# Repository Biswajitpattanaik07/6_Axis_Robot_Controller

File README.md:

# Axion: 6-Axis Robot Arm Controller

Axion is an open-source controller board for a 6-axis articulated robot arm. It is built around an **STM32F103C8T6** and combines six servo outputs, six per-joint IMU inputs, and three ways to talk to the outside world: USB, CAN bus, and an NRF24L01 wireless link.

The whole board runs from a single **12 V** input. Everything else (5 V for servos and logic, 3.3 V for the MCU and radio) is generated on board.

---

## Table of contents

1. [Features](#features)
2. [System overview](#system-overview)
3. [Hardware details](#hardware-details)
4. [Pin mapping](#pin-mapping)
5. [Power design notes](#power-design-notes)
6. [PCB gallery](#pcb-gallery)
7. [Repository structure](#repository-structure)
8. [Bill of materials](#bill-of-materials)
9. [Getting started](#getting-started)
10. [Firmware](#firmware)
11. [Known limitations and design notes](#known-limitations-and-design-notes)
12. [Roadmap](#roadmap)
13. [Contributing](#contributing)
14. [License](#license)

---

## Features

| Area | What the board provides |
|---|---|
| Controller | STM32F103C8T6 (ARM Cortex-M3) |
| Servo outputs | 6 channels, each with its own MOSFET driver stage |
| Orientation feedback | 6 I2C headers, one per joint, for IMUs |
| USB | CP2102N USB-to-UART bridge |
| CAN | TCAN330 CAN transceiver |
| Wireless | NRF24L01 socket |
| Power input | 12 V |
| 5 V rail | TPS5331x buck converter |
| 3.3 V rail | LM3480 linear regulator |
| Programming and debug | SWD header |
| Design files | KiCad project, open hardware |

---

## System overview

```mermaid
flowchart LR
    PSU[12 V input] --> BUCK[TPS5331x buck]
    BUCK -->|5 V| SERVO[Servo headers x6]
    BUCK -->|5 V| LDO[LM3480]
    LDO -->|3.3 V| MCU[STM32F103C8T6]
    LDO -->|3.3 V| NRF[NRF24L01 socket]
    LDO -->|3.3 V| CAN[TCAN330]
    MCU -->|PWM| MOS[MOSFET driver stages x6]
    MOS --> SERVO
    MCU <-->|I2C| IMU[IMU headers x6]
    MCU <-->|UART| USB[CP2102N USB]
    MCU <-->|CAN| CAN
    MCU <-->|SPI| NRF
    PROG[SWD header] --- MCU
```

Typical use: a host (PC over USB, another node over CAN, or a handheld over NRF24L01) sends joint targets. The MCU generates the servo PWM signals and reads the joint IMUs to track the arm's real orientation.

---

## Hardware details

### Main controller

The STM32F103C8T6 provides the PWM timers, I2C, SPI, UART and CAN peripherals this board needs. It is programmed and debugged over the SWD header.

### Servo outputs

Six servo channels, one per joint. Each channel has its own MOSFET driver stage between the MCU pin and the servo header, so the MCU only drives a gate rather than the servo signal line directly.

### IMU headers

Six I2C headers, one per joint. A mounted IMU at each joint lets the firmware measure the actual orientation of every link instead of trusting commanded angles.

> **Addressing:** many IMUs offer only two I2C addresses, so six on one bus will conflict. TBD: describe how this board resolves it (multiplexer, separate buses, or address strapping).

### Communication

| Interface | Part | Use |
|---|---|---|
| USB | CP2102N | Host connection, firmware console, command interface |
| CAN | TCAN330 | Multi-node or robust wired control |
| Wireless | NRF24L01 socket | Remote or handheld control |

### Power

| Stage | Part | Input | Output |
|---|---|---|---|
| Buck converter | TPS5331x | 12 V | 5 V |
| Linear regulator | LM3480 | 5 V | 3.3 V |

---

## Pin mapping

Fill this in from the schematic.

| Function | Signal | MCU pin | Notes |
|---|---|---|---|
| Servo 1 | PWM | TBD | MOSFET stage |
| Servo 2 | PWM | TBD | MOSFET stage |
| Servo 3 | PWM | TBD | MOSFET stage |
| Servo 4 | PWM | TBD | MOSFET stage |
| Servo 5 | PWM | TBD | MOSFET stage |
| Servo 6 | PWM | TBD | MOSFET stage |
| I2C | SCL / SDA | TBD | Shared by IMU headers |
| USB-UART | TX / RX | TBD | CP2102N |
| CAN | TX / RX | TBD | TCAN330 |
| NRF24L01 | SCK / MISO / MOSI / CSN / CE / IRQ | TBD | SPI |
| Debug | SWDIO / SWCLK | PA13 / PA14 | SWD header |

---

## Power design notes

| Rail | Source | Feeds |
|---|---|---|
| 12 V | External supply | Buck converter input |
| 5 V | TPS5331x | Servos, 5 V logic, LM3480 input |
| 3.3 V | LM3480 | MCU, NRF24L01, TCAN330, IMUs |

Things to check for your own build:

- **Servo current.** Hobby servos can draw well over 1 A each under load, and stall current is higher. Size the 12 V supply and the buck converter for the worst-case total, not the average.
- **Buck converter parts.** Confirm the inductor saturation current, input and output capacitors, and trace widths against the load.
- **3.3 V budget.** The LM3480 is a small linear regulator. Add up the MCU, NRF24L01, CAN transceiver and IMUs and compare with its rated output current.
- **NRF24L01 noise.** The radio is sensitive to supply noise. Keep decoupling capacitors close to its socket.
- **Servo transients.** Bulk capacitance near the servo headers helps stop current spikes from resetting the MCU.
- **Grounding.** Keep high-current servo return paths away from the MCU and IMU ground region.

---

## PCB gallery

| Board, view 1 | Board, view 2 |
|---|---|
|  |  |

| Front copper | Back copper |
|---|---|
|  |  |

---

## Repository structure

```
6_Axis_Robot_Controller/
├── Assets/                    # Banner used in this README
├── Pics/                      # Board photos and renders
├── RoProp.kicad_pcb           # KiCad PCB layout
├── RoProp.kicad_pcb-bak       # KiCad automatic backup
├── RoProp-cache.lib           # KiCad schematic symbol cache
├── RoProp-page-001.jpg        # Schematic page image
├── .gitignore
└── README.md
```

The KiCad project files use the working name **RoProp**. Other KiCad files (schematic, project file) sit in the repository root alongside these.

Planned additions: `gerbers/` for fabrication outputs, `bom/` for the bill of materials, `docs/` for the pinout and design notes, and `firmware/` for the STM32 code.

---

## Bill of materials

Key parts. A full BOM (designators, values, footprints and supplier part numbers) is still to be added.

| Part | Function |
|---|---|
| STM32F103C8T6 | Main microcontroller |
| CP2102N | USB-to-UART bridge |
| TCAN330 | CAN transceiver |
| NRF24L01 module | 2.4 GHz wireless link |
| TPS5331x | 12 V to 5 V buck converter |
| LM3480 | 5 V to 3.3 V regulator |
| MOSFETs (x6) | Servo driver stages |

---

## Getting started

### 1. Get the board made

1. Clone the repository and open the `RoProp` project in KiCad to review or modify the design.
2. Export Gerber and drill files from the PCB editor (File > Fabrication Outputs) and send them to a PCB manufacturer.
3. Order the parts from the bill of materials and solder the board.

### 2. Bring-up checklist

Do these in order, with a current-limited bench supply.

1. Visually inspect the board for solder bridges, especially around the buck converter and MCU.
2. Check for shorts between 12 V, 5 V, 3.3 V and ground before powering on.
3. Apply 12 V with a low current limit and check that the 5 V rail is correct.
4. Check that the 3.3 V rail is correct.
5. Connect an SWD programmer (for example an ST-Link) and confirm the MCU is detected.
6. Flash a simple LED blink or UART test.
7. Test each servo output separately, with no mechanical load first.
8. Connect IMUs and scan the I2C bus.
9. Test USB, CAN and the NRF24L01 link.

### 3. Connect the hardware

| Connector | What to connect |
|---|---|
| 12 V input | Power supply sized for your servos |
| Servo headers 1 to 6 | One servo per arm joint |
| IMU headers 1 to 6 | One IMU per joint |
| USB | Host computer |
| CAN | CAN bus (check termination) |
| SWD | Programmer |

---

## Firmware

Firmware is a work in progress. Planned structure:

```
firmware/
├── src/
│   ├── main.c
│   ├── servo.c        # PWM generation for 6 channels
│   ├── imu.c          # I2C reads, per-joint orientation
│   ├── comms_usb.c    # UART command interface
│   ├── comms_can.c    # CAN messages
│   └── comms_nrf.c    # NRF24L01 link
└── README.md
```

Planned build and flash steps:

```bash
cd firmware
# build command here
# flash command here (for example with st-flash or OpenOCD)
```

Planned features:

- Smooth, rate-limited servo motion
- Per-joint orientation from the IMUs
- A simple command protocol shared by USB, CAN and the radio link
- Forward and inverse kinematics for the arm

---

## Known limitations and design notes

This is a first prototype. Open points worth tracking as issues:

- [ ] Verify the 5 V buck converter against the real total servo current
- [ ] Verify the 3.3 V budget with the radio and all IMUs fitted
- [ ] Confirm the IMU addressing scheme for six devices
- [ ] Confirm CAN bus termination options
- [ ] Add reverse-polarity and overcurrent protection on the 12 V input if not already present

---

## Roadmap

- [x] PCB design in KiCad
- [ ] Order and assemble prototype
- [ ] Board bring-up and validation
- [ ] Basic firmware: servo control and IMU reads
- [ ] CAN and wireless command interface
- [ ] Kinematics and motion planning
- [ ] Mechanical design and full arm assembly
- [ ] Documentation and demo video

---

## Contributing

Contributions are welcome. Useful areas:

- Review of the power delivery for multi-servo setups
- Layout and routing feedback
- Firmware
- Documentation and test results from your own builds

Open an issue to discuss a change, or submit a pull request.

---

## License

Add a `LICENSE` file before publishing. Common open-hardware choices are CERN-OHL-P or CERN-OHL-S for the hardware, and MIT or Apache-2.0 for the firmware.

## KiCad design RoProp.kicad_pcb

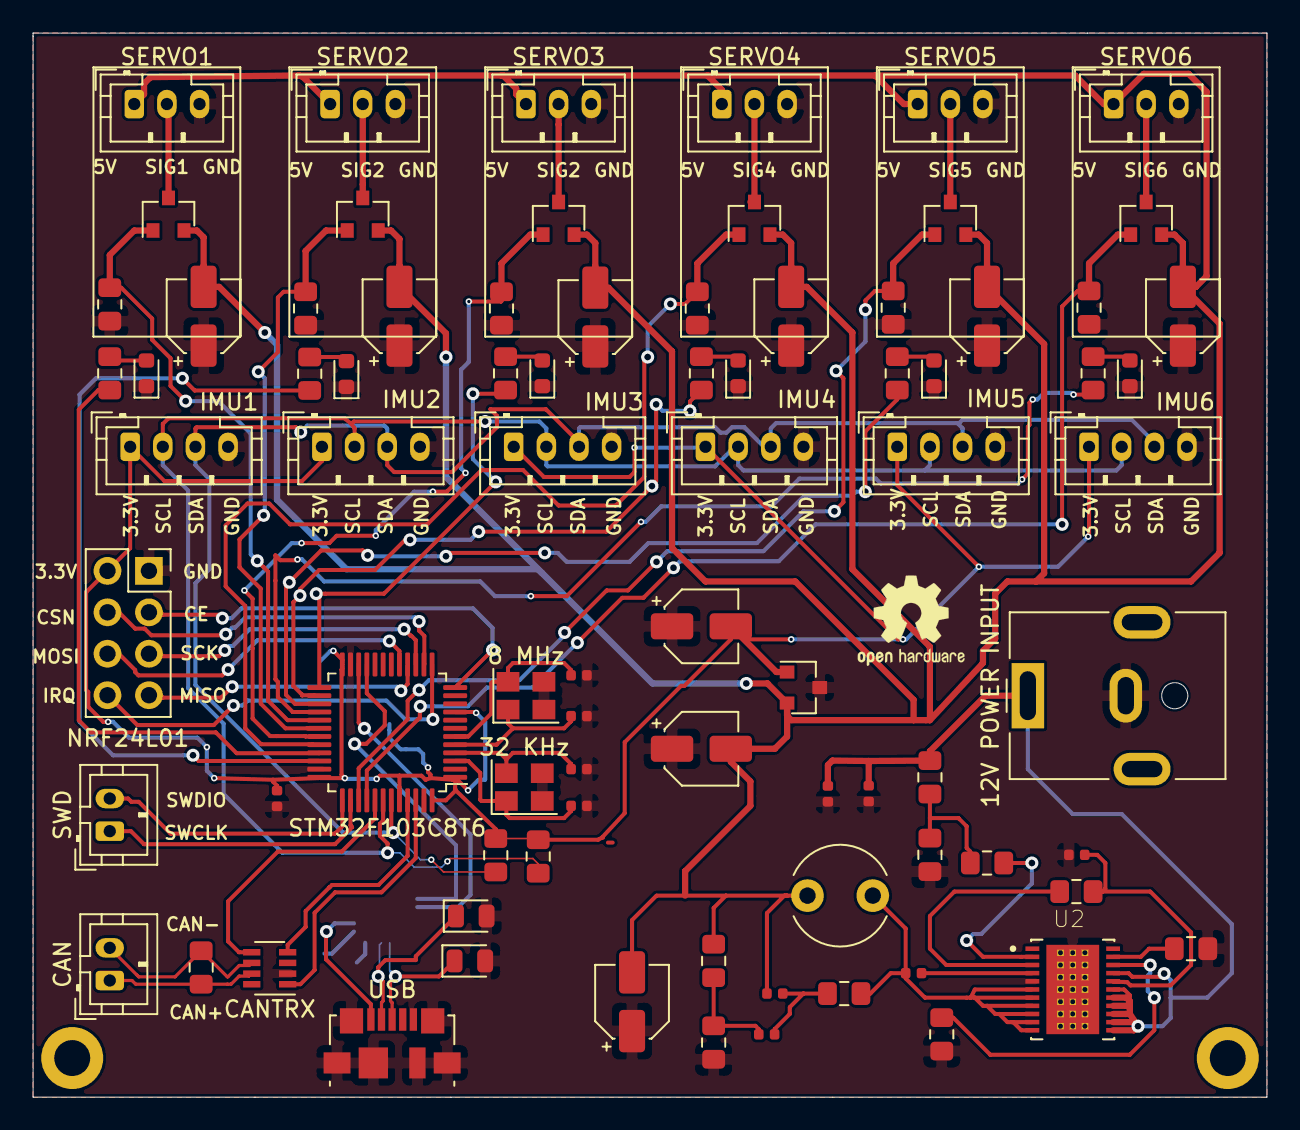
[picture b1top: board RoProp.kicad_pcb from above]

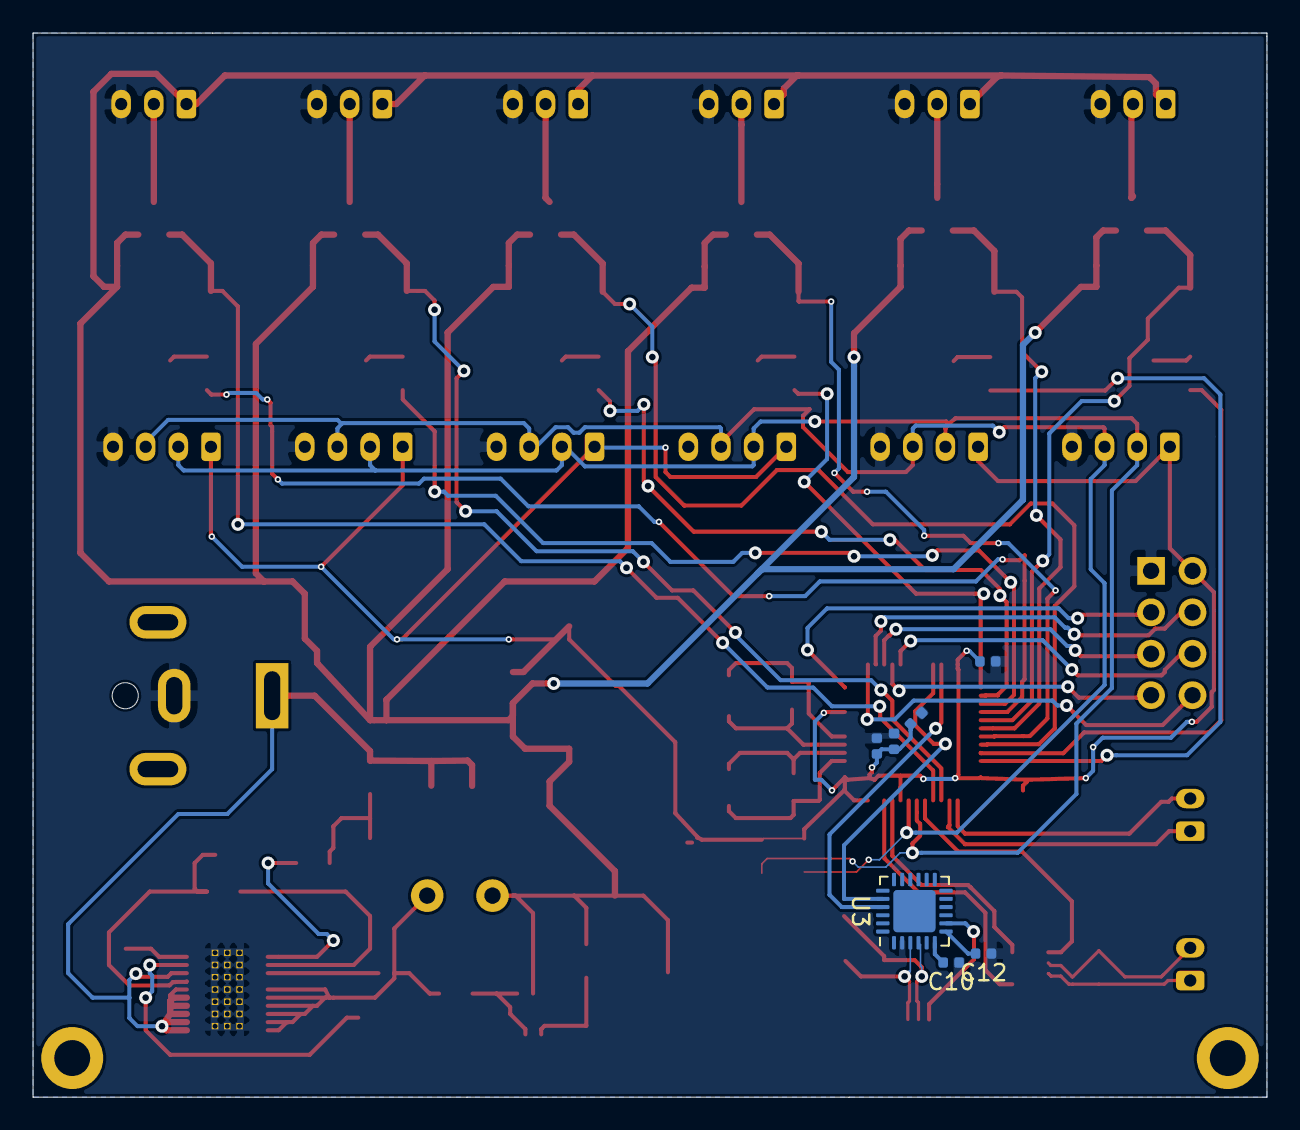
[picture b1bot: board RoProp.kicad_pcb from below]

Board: 2 copper layers, 75.6 x 65.2 mm, 89 parts (7 on the bottom side), 62 nets.

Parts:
8 MHz, 32 KHz: Crystal_GND23; Crystal_SMD_Abracon_ABM8G-4Pin_3.2x2.5mm
12V POWER INPUT: Barrel_Jack; BarrelJack_CUI_PJ-063AH_Horizontal
C1, C2: 4.7U; C_0402_1005Metric
C3, C4, C5, C6, C7: 10N; C_0402_1005Metric
C8: 1U; C_0402_1005Metric
C9, C17: 100N; C_0402_1005Metric
C10, C11, C12, C13, C14, C15, C16: 1N; C_0402_1005Metric
C18: 100U; CP_Elec_4x3
C19, C23: 1N; CP_Elec_4x3
C20, C21, C22, C24, C25, C26: 2U; CP_Elec_4x3
CAN: Conn_01x02; JST_PH_B2B-PH-K_1x02_P2.00mm_Vertical
CANTRX: TCAN330; SOT-23-8
D1, D2, D3, D4, D5, D6: LED; LED_0603_1608Metric
D7, D8: D_TVS; D_0805_2012Metric
IMU1, IMU2, IMU3, IMU4, IMU5, IMU6: Conn_01x04; JST_PH_B4B-PH-K_1x04_P2.00mm_Vertical
L1: 4.7U; L_Radial_D6.0mm_P4.00mm
NRF24L01: Conn_02x04_Odd_Even; PinSocket_2x04_P2.54mm_Vertical
Q1, Q2, Q3, Q4, Q5, Q6: DMN2056U; SOT-23
R1, R2: 4.7K; R_0805_2012Metric_Pad1.15x1.40mm_HandSolder
R3: 854K; R_0805_2012Metric_Pad1.15x1.40mm_HandSolder
R4: 86.6K; R_0805_2012Metric_Pad1.15x1.40mm_HandSolder
R5: 1K; R_0805_2012Metric_Pad1.15x1.40mm_HandSolder
R6, R7, R11: 105K; R_0805_2012Metric_Pad1.15x1.40mm_HandSolder
R8, R9, R10, R12, R13, R14, R15: 1.91K; R_0805_2012Metric_Pad1.15x1.40mm_HandSolder
R16: 69.8K; R_0805_2012Metric_Pad1.15x1.40mm_HandSolder
R17: 10K; R_0805_2012Metric_Pad1.15x1.40mm_HandSolder
R18, R19, R20, R21, R22, R23: 2k; R_0805_2012Metric_Pad1.15x1.40mm_HandSolder
R24: 120; R_0805_2012Metric_Pad1.15x1.40mm_HandSolder
SERVO1, SERVO2, SERVO3, SERVO4, SERVO5, SERVO6: Conn_01x03; JST_PH_B3B-PH-K_1x03_P2.00mm_Vertical
STM32F103C8T6: STM32F103C8Tx; LQFP-48_7x7mm_P0.5mm
SWD: Conn_01x02; JST_PH_B2B-PH-K_1x02_P2.00mm_Vertical
U2: TPS53318DQPR; CONV_TPS53318DQPR
U3: CP2102N-A01-GQFN24; QFN-24-1EP_4x4mm_P0.5mm_EP2.6x2.6mm
U4: LM3480-3.3; SOT-23
USB: USB_B_Micro; USB_Micro-B_Molex_47346-0001

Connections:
+3V3: C3.1, C4.1, C5.2, C6.2, C7.2, C10.2, C12.2, C23.2, CANTRX.3, IMU1.1, IMU2.1, IMU3.1, IMU4.1, IMU5.1, IMU6.1, NRF24L01.2, R1.1, R2.1, STM32F103C8T6.1, STM32F103C8T6.9, STM32F103C8T6.24, STM32F103C8T6.36, STM32F103C8T6.44, STM32F103C8T6.48, U3.5, U3.6, U3.7, U4.1
+5V: C17.1, C18.2, C19.2, C20.2, C21.2, C22.2, C24.2, C25.2, C26.2, L1.2, Q1.2, Q2.2, Q3.2, Q4.2, Q5.2, Q6.2, R16.2, SERVO1.1, SERVO2.1, SERVO3.1, SERVO4.1, SERVO5.1, SERVO6.1, U4.2
/CAN+: CAN.1, CANTRX.7, R24.1
/CAN-: CAN.2, CANTRX.6, R24.2
/CANRX: CANTRX.4, STM32F103C8T6.45
/CANTX: CANTRX.1, STM32F103C8T6.46
/CE: NRF24L01.3, STM32F103C8T6.12
/CSN: NRF24L01.4, STM32F103C8T6.14
/D+: D8.1, U3.3, USB.3
/D-: D7.1, U3.4, USB.2
/IRQ: NRF24L01.8, STM32F103C8T6.13
/LED1: R8.2, STM32F103C8T6.33
/LED2: R9.2, STM32F103C8T6.34
/LED3: R10.2, STM32F103C8T6.25
/LED4: R12.2, STM32F103C8T6.26
/LED5: R13.2, STM32F103C8T6.27
/LED6: R14.2, STM32F103C8T6.28
/MISO: NRF24L01.7, STM32F103C8T6.16
/MOSI: NRF24L01.6, STM32F103C8T6.17
/OSC_8_IN: 8 MHz.1, C16.1, STM32F103C8T6.5
/OSC_8_OUT: 8 MHz.4, C14.1, STM32F103C8T6.6
/OSC_32_IN: 32 KHz.1, C15.1, STM32F103C8T6.3
/OSC_32_OUT: 32 KHz.4, C13.1, STM32F103C8T6.4
/PWM1: Q1.1, R18.1, STM32F103C8T6.29
/PWM2: Q4.1, R21.1, STM32F103C8T6.30
/PWM3: Q2.1, R19.1, STM32F103C8T6.31
/PWM4: Q5.1, R22.1, STM32F103C8T6.32
/PWM5: Q3.1, R20.1, STM32F103C8T6.39
/PWM6: Q6.1, R23.1, STM32F103C8T6.40
/RX: STM32F103C8T6.22, U3.21
/SCK: NRF24L01.5, STM32F103C8T6.15
/SCL: IMU1.2, IMU2.2, IMU3.2, IMU4.2, IMU5.2, IMU6.2, R1.2, STM32F103C8T6.42
/SDA: IMU1.3, IMU2.3, IMU3.3, IMU4.3, IMU5.3, IMU6.3, R2.2, STM32F103C8T6.43
/SERVO1: Q1.3, SERVO1.2
/SERVO2: Q4.3, SERVO2.2
/SERVO3: Q2.3, SERVO3.2
/SERVO4: Q5.3, SERVO4.2
/SERVO5: Q3.3, SERVO5.2
/SERVO6: Q6.3, SERVO6.2
/SHDN: CANTRX.5, STM32F103C8T6.41
/SWCLK: STM32F103C8T6.38, SWD.1
/SWDIO: STM32F103C8T6.37, SWD.2
/TX: STM32F103C8T6.21, U3.20
/VBUS: U3.8, USB.1
/VFB: C11.2, R16.1, R17.2, U2.1
/VIN: 12V POWER INPUT.1, C1.2, C2.2, R3.1, U2.12, U2.13, U2.14, U2.15, U2.16, U2.17, U2.19
GND: 8 MHz.2, 8 MHz.3, 12V POWER INPUT.2, 32 KHz.2, 32 KHz.3, C1.1, C2.1, C3.2, C4.2, C5.1, C6.1, C7.1, C8.1, C10.1, C12.1, C13.2, C14.2, C15.2, C16.2, C18.1, C19.1, C20.1, C21.1, C22.1, C23.1, C24.1, C25.1, C26.1, CANTRX.2, D1.1, D2.1, D3.1, D4.1, D5.1, D6.1, D7.2, D8.2, IMU1.4, IMU2.4, IMU3.4, IMU4.4, IMU5.4, IMU6.4, NRF24L01.1, R4.2, R6.2, R7.2, R17.1, R18.2, R19.2, R20.2, R21.2, R22.2, R23.2, SERVO1.3, SERVO2.3, SERVO3.3, SERVO4.3, SERVO5.3, SERVO6.3, STM32F103C8T6.7, STM32F103C8T6.8, STM32F103C8T6.23, STM32F103C8T6.35, STM32F103C8T6.47, U2.5, U2.23, U2.TV1, U2.TV2, U2.TV3, U2.TV4, U2.TV5, U2.TV6, U2.TV7, U2.TV8, U2.TV9, U2.TV10, U2.TV11, U2.TV12, U2.TV13, U2.TV14, U2.TV15, U2.TV16, U2.TV17, U2.TV18, U2.TV19, U2.TV20, U2.TV21, U3.2, U3.25, U4.3, USB.5, USB.6
unnamed: C8.2, R11.2, U2.18
unnamed: C9.1, L1.1, R15.2, U2.6, U2.7, U2.8, U2.9, U2.10, U2.11
unnamed: C9.2, U2.4
unnamed: C11.1, C17.2, R15.1
unnamed: D1.2, R8.1
unnamed: D2.2, R9.1
unnamed: D3.2, R10.1
unnamed: D4.2, R12.1
unnamed: D5.2, R13.1
unnamed: D6.2, R14.1
unnamed: R3.2, R4.1, R5.1
unnamed: R5.2, U2.2
unnamed: R6.1, U2.20
unnamed: R7.1, U2.21
unnamed: R11.1, U2.3
